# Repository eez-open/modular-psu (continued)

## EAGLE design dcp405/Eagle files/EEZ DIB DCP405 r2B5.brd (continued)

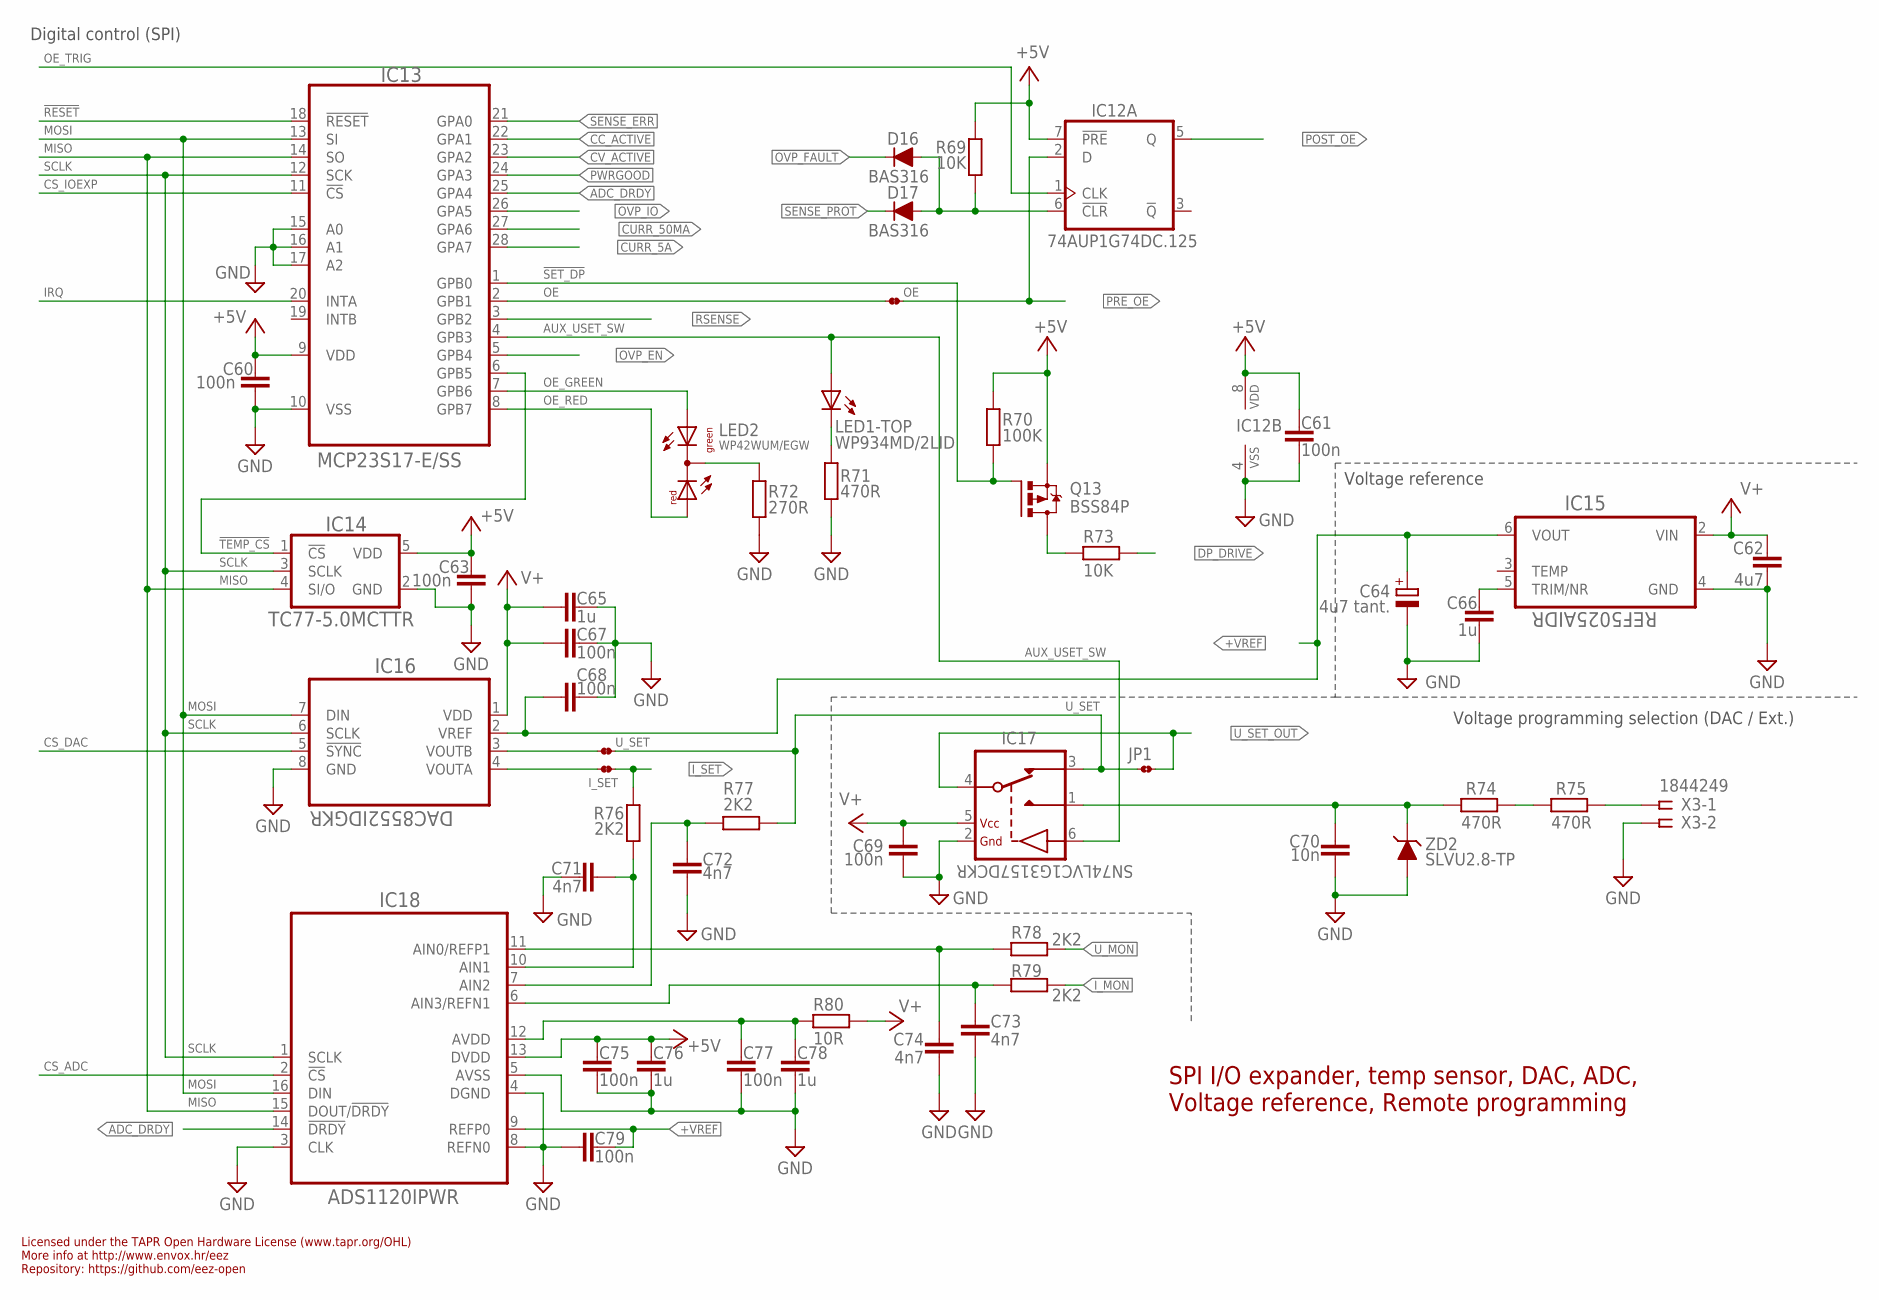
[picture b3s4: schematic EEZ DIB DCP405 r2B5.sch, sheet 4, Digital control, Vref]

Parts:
C60, C61, C63, C67, C68, C69, C75, C77, C79: 100n; C0603
C62: 4u7; C1206
C64: 4u7 tant.; EC1206
C65, C66, C76, C78: 1u; C0805
C70: 10n; C0805
C71, C72, C73, C74: 4n7; C0805
D16, D17: BAS316; SOD323-R
IC12: 74AUP1G74DC.125; DCU8
IC13: MCP23S17-E/SS; SOP65P780X200-28N
IC14: TC77-5.0MCTTR; SOT23-5
IC15: REF5025AIDR; SOIC127P600X175-8N
IC16: DAC8552IDGKR; DGK8-M
IC17: SN74LVC1G3157DCKR; SOT65P210X110-6N
IC18: ADS1120IPWR; PW(R-PDSO-G16)
I_SET: JP2-NOCUT
JP1: JP2-CUT
LED1: WP934MD/2LID; WP934MD
LED2: WP42WUM/EGW; L-42WUM-1EGWT
OE: JP2-NOCUT
Q13: BSS84P; SOT95P237X112-3N
R69, R73: 10K; R0805
R70: 100K; R0805
R71, R74, R75: 470R; R0805
R72: 270R; R0805
R76, R77, R78, R79: 2K2; R0805
R80: 10R; R1206
U_SET: JP2-NOCUT
X3: 1844249; MC1,5/5-G-3,5
ZD2: SLVU2.8-TP; SOT23

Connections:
!ADC_DRDY: IC13.25 (GPA4), IC18.14 (!DRDY)
!DP_DRIVE: R73.1; also elsewhere on the board
!OVP_FAULT: D16.C; also elsewhere on the board
!RESET: IC13.18 (!RESET); also elsewhere on the board
!SET_DP: IC13.1 (GPB0), Q13.1 (G), R70.2
!TEMP_CS: IC13.6 (GPB5), IC14.1 (!CS)
+5V: C60.1, C61.2, C63.1, C75.2, C76.2, IC12.7 (!PRE), IC12.8 (VDD), IC13.9 (VDD), IC14.5 (VDD), IC18.13 (DVDD), Q13.2 (S), R69.1, R70.1; also elsewhere on the board
+VREF: C64.+, C68.2, C79.2, IC15.6 (VOUT), IC16.2 (VREF), IC18.9 (REFP0); also elsewhere on the board
AUX_IN: C70.2, IC17.1 (NO), R74.1, ZD2.3 (C)
AUX_USET_SW: IC13.4 (GPB3), IC17.6 (CTRL), LED1.TA (A)
CC_ACTIVE: IC13.22 (GPA1); also elsewhere on the board
CS_ADC: IC18.2 (!CS); also elsewhere on the board
CS_DAC: IC16.5 (!SYNC); also elsewhere on the board
CS_IOEXP: IC13.11 (!CS); also elsewhere on the board
CURR_5A: IC13.28 (GPA7); also elsewhere on the board
CURR_50MA: IC13.27 (GPA6); also elsewhere on the board
CV_ACTIVE: IC13.23 (GPA2); also elsewhere on the board
DP_LED: Q13.3 (D), R73.2
GND: C60.2, C61.1, C62.2, C63.2, C64.-, C65.2, C66.2, C67.1, C68.1, C69.2, C70.1, C71.1, C72.1, C73.2, C74.1, C75.1, C76.1, C77.1, C78.1, C79.1, IC12.4 (VSS), IC13.10 (VSS), IC13.15 (A0), IC13.16 (A1), IC13.17 (A2), IC14.2 (GND), IC15.4 (GND), IC16.8 (GND), IC17.2 (GND), IC18.3 (CLK), IC18.4 (DGND), IC18.5 (AVSS), IC18.8 (REFN0), R71.1, R72.2, X3.2, ZD2.1 (A), ZD2.2 (A); also elsewhere on the board
IRQ: IC13.20 (INTA); also elsewhere on the board
I_MON: R79.1; also elsewhere on the board
I_SET: I_SET.2, R76.1; also elsewhere on the board
MISO: IC13.14 (SO), IC14.4 (SI/O), IC18.15 (DOUT/!DRDY); also elsewhere on the board
MOSI: IC13.13 (SI), IC16.7 (DIN), IC18.16 (DIN); also elsewhere on the board
unnamed: LED2.CC (C), R72.1
unnamed: IC16.4 (VOUTA), I_SET.1
unnamed: R74.2, R75.1
unnamed: R75.2, X3.1
unnamed: IC16.3 (VOUTB), U_SET.1
unnamed: D16.A, D17.A, IC12.6 (!CLR), R69.2
unnamed: C77.2, C78.2, IC18.12 (AVDD), R80.2
unnamed: C66.1, IC15.5 (TRIM/NR)
unnamed: C71.2, IC18.10 (AIN1), R76.2
unnamed: C74.2, IC18.11 (AIN0/REFP1), R78.2
unnamed: C72.2, IC18.7 (AIN2), R77.2
unnamed: C73.1, IC18.6 (AIN3/REFN1), R79.2
unnamed: LED1.TC (C), R71.2
OE: IC13.2 (GPB1), OE.1
OE_GREEN: IC13.7 (GPB6), LED2.GREEN (AG)
OE_RED: IC13.8 (GPB7), LED2.RED (AR)
OE_TRIG: IC12.1 (CLK); also elsewhere on the board
OVP_EN: IC13.5 (GPB4); also elsewhere on the board
OVP_IO: IC13.26 (GPA5); also elsewhere on the board
POST_OE: IC12.5 (Q); also elsewhere on the board
PRE_OE: IC12.2 (D), OE.2; also elsewhere on the board
PWRGOOD: IC13.24 (GPA3); also elsewhere on the board
RSENSE: IC13.3 (GPB2); also elsewhere on the board
SCLK: IC13.12 (SCK), IC14.3 (SCLK), IC16.6 (SCLK), IC18.1 (SCLK); also elsewhere on the board
SENSE_ERR: IC13.21 (GPA0); also elsewhere on the board
SENSE_PROT: D17.C; also elsewhere on the board
U_MON: R78.1; also elsewhere on the board
U_SET: IC17.3 (NC), JP1.1, R77.1, U_SET.2; also elsewhere on the board
U_SET_OUT: IC17.4 (COM), JP1.2; also elsewhere on the board
V+: C62.1, C65.1, C67.2, C69.1, IC15.2 (VIN), IC16.1 (VDD), IC17.5 (VDD), R80.1; also elsewhere on the board

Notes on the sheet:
Digital control (SPI)
Voltage reference
Licensed under the TAPR Open Hardware License (www.tapr.org/OHL)
Repository: https://github.com/eez-open
More info at http://www.envox.hr/eez
SPI I/O expander, temp sensor, DAC, ADC, Voltage reference, Remote programming
Voltage programming selection (DAC / Ext.)

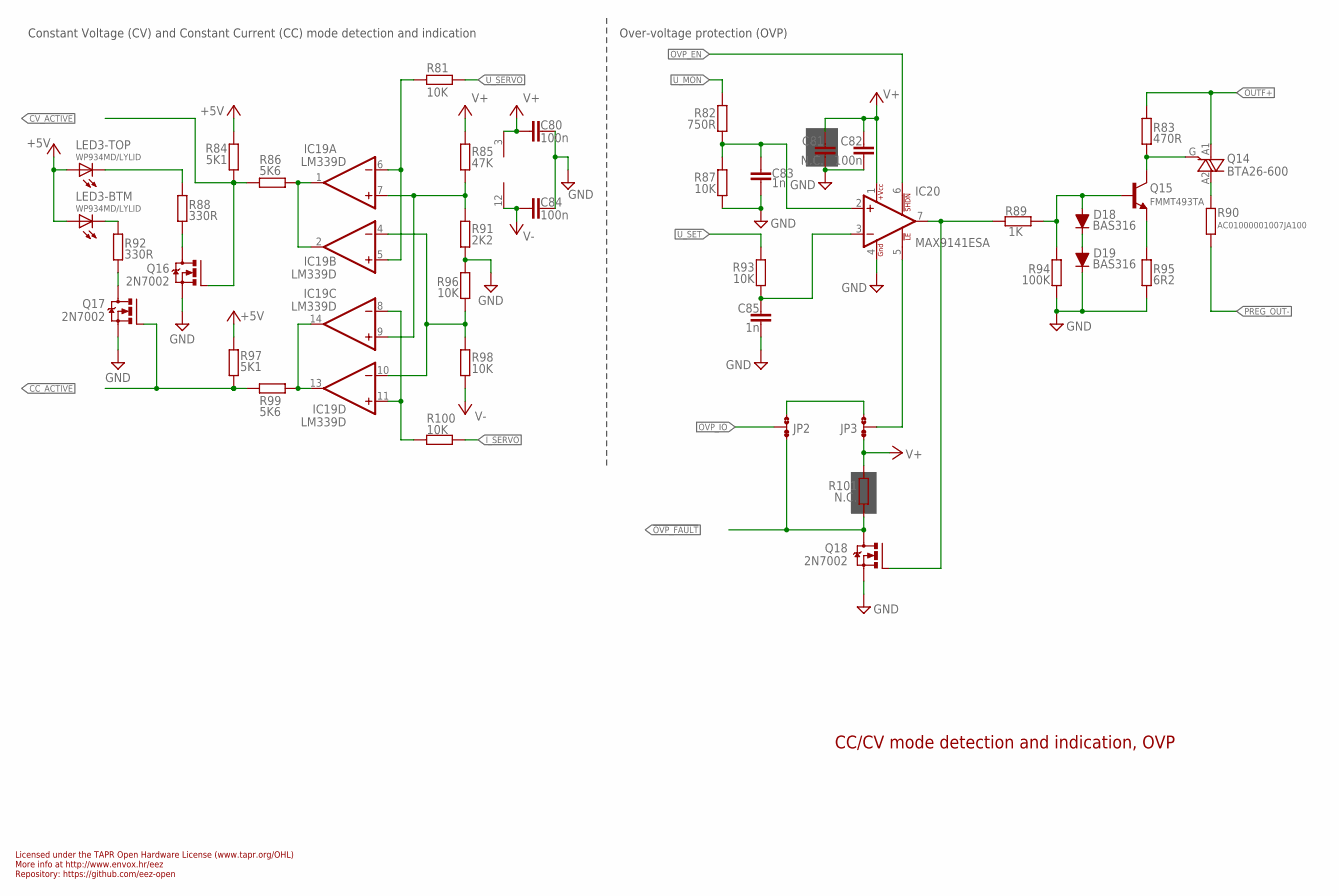
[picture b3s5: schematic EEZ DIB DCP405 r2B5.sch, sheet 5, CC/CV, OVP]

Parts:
C80, C82, C84: 100n; C0603
C81: N.C.; C0805
C83, C85: 1n; C0805
D18, D19: BAS316; SOD323-R
IC19: LM339D; SOIC127P600X175-14N
IC20: MAX9141ESA; SOIC127P600X173-8N
JP2: JP3-CUT-ROTATED; JP3-CUT2
JP3: JP3-CUT
LED3: WP934MD/LYLID; WP934MD
Q14: BTA26-600; TOP3_TRIAC_NOHOLE
Q15: FMMT493TA; SOT23-BEC
Q16, Q17: 2N7002; SOT103P240X110-3N
Q18: 2N7002; SOT103P240X110-3N; MPN 2N7002-7-F
R81, R87, R93, R96, R98, R100: 10K; R0805
R82: 750R; R0805
R83: 470R; R0805
R84, R97: 5K1; R0805
R85: 47K; R0805
R86, R99: 5K6; R0805
R88, R92: 330R; R0805
R89: 1K; R0805
R90: AC01000001007JA100; 0411/15
R91: 2K2; R0805
R94: 100K; R0805
R95: 6R2; R0805
R101: N.C.; R0805

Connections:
!OVP_FAULT: JP2.NC, Q18.3 (D), R101.2; also elsewhere on the board
+5V: LED3.BA (A), LED3.TA (A), R84.2, R97.2; also elsewhere on the board
CC_ACTIVE: Q17.1 (G), R97.1, R99.2; also elsewhere on the board
CC_LED: LED3.BC (C), R92.2
CV_ACTIVE: Q16.1 (G), R84.1, R86.2; also elsewhere on the board
CV_LED: LED3.TC (C), R88.1
GND: C80.1, C81.2, C82.1, C83.1, C84.1, C85.1, D19.C, IC20.4 (GND), Q16.2 (S), Q17.2 (S), Q18.2 (S), R87.2, R91.1, R94.1, R95.1, R96.2; also elsewhere on the board
I_SERVO: R100.1; also elsewhere on the board
unnamed: IC20.7 (OUT), Q18.1 (G), R89.2
unnamed: Q14.A2, R90.2
unnamed: Q14.G, Q15.C, R83.1
unnamed: Q15.E, R95.2
unnamed: D18.C, D19.A
unnamed: D18.A, Q15.B, R89.1, R94.2
unnamed: C85.2, IC20.3 (-IN), R93.2
unnamed: C83.2, IC20.2 (+IN), R82.2, R87.1
unnamed: Q17.3 (D), R92.1
unnamed: JP2.NO, JP3.NO
unnamed: IC20.5 (!LE), JP3.COM
unnamed: IC19.1 (OUT), IC19.2 (OUT), R86.1
unnamed: IC19.13 (OUT), IC19.14 (OUT), R99.1
unnamed: Q16.3 (D), R88.2
unnamed: IC19.5 (+IN), IC19.6 (-IN), R81.2
unnamed: IC19.8 (-IN), IC19.11 (+IN), R100.2
unnamed: IC19.7 (+IN), IC19.9 (+IN), R85.1, R91.2
unnamed: IC19.4 (-IN), IC19.10 (-IN), R96.1, R98.2
OUTF+: Q14.A1, R83.2; also elsewhere on the board
OVP_EN: IC20.6 (!SHDN); also elsewhere on the board
OVP_IO: JP2.COM; also elsewhere on the board
PREG_OUT-: R90.1; also elsewhere on the board
U_MON: R82.1; also elsewhere on the board
U_SERVO: R81.1; also elsewhere on the board
U_SET: R93.1; also elsewhere on the board
V+: C80.2, C81.1, C82.2, IC19.3 (V+), IC20.1 (+VCC), JP3.NC, R85.2, R101.1; also elsewhere on the board
V-: C84.2, IC19.12 (GND), R98.1; also elsewhere on the board

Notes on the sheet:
Licensed under the TAPR Open Hardware License (www.tapr.org/OHL)
Repository: https://github.com/eez-open
More info at http://www.envox.hr/eez
CC/CV mode detection and indication, OVP
Constant Voltage (CV) and Constant Current (CC) mode detection and indication
Over-voltage protection (OVP)

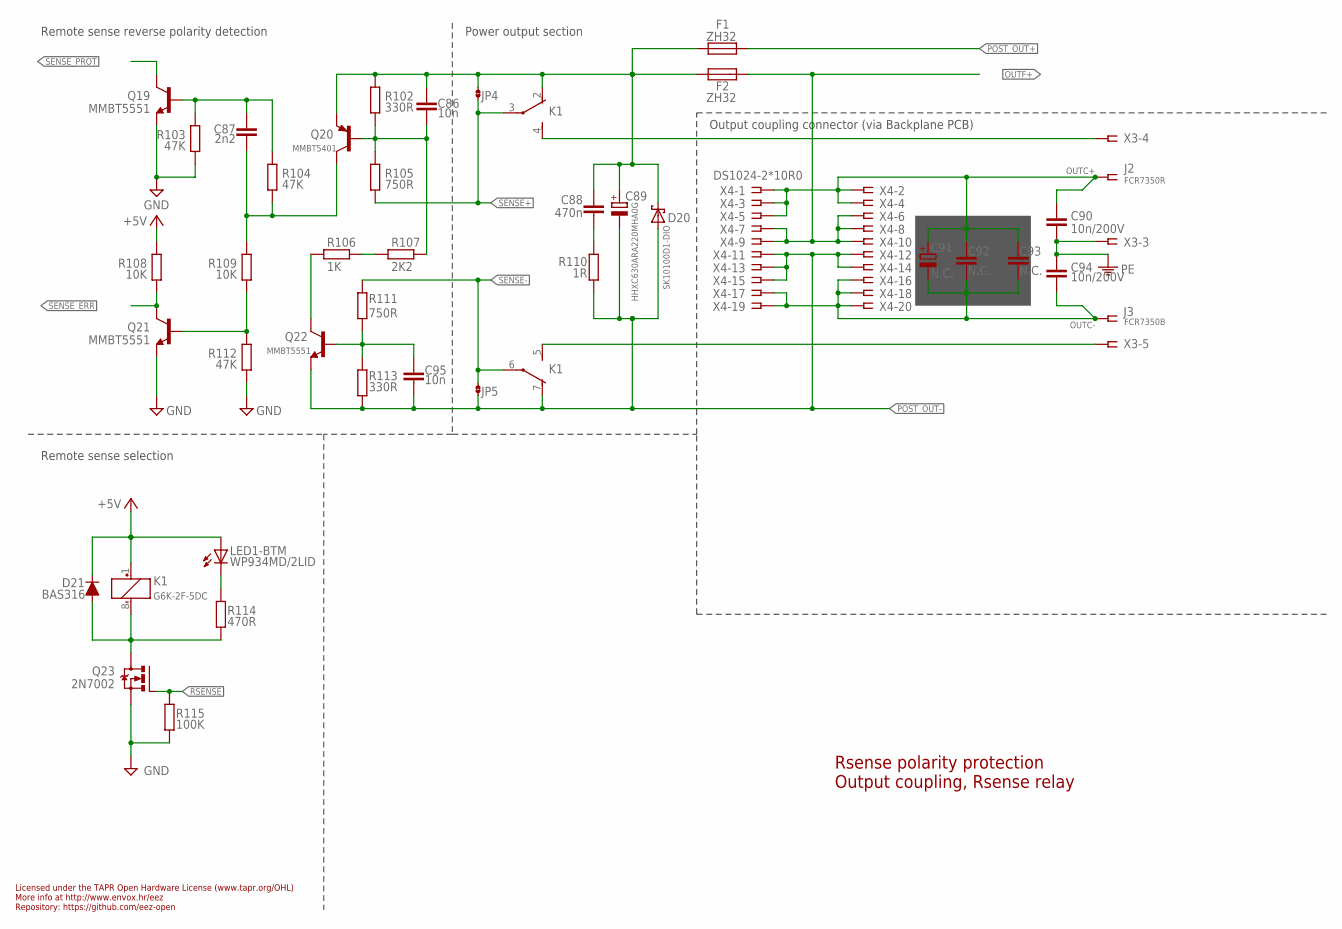
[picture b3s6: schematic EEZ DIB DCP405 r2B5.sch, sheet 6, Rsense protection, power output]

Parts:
C86, C95: 10n; C0805
C87: 2n2; C0805
C88: 470n; C1206
C89: HHXC630ARA220MHA0G; CAPAE830X1050N
C90, C94: 10n/200V; C1206
C91: N.C.; ECAP2/5
C92, C93: N.C.; C0805
D20: SK10100D1-DIO; TO252-L
D21: BAS316; SOD323-R
F1, F2: ZH32
J2: FCR7350R; S16N-PC
J3: FCR7350B; S16N-PC
JP4, JP5: JP2-CUT
K1: G6K-2F-5DC; G6K-2F; MPN G6K-2F DC24
LED1: WP934MD/2LID; WP934MD
Q19, Q21, Q22: MMBT5551; SOT23-BEC
Q20: MMBT5401; SOT23-BEC
Q23: 2N7002; SOT103P240X110-3N; MPN 2N7002-7-F
R102, R113: 330R; R0805
R103, R104, R112: 47K; R0805
R105, R111: 750R; R0805
R106: 1K; R0805
R107: 2K2; R0805
R108, R109: 10K; R0805
R110: 1R; R0805
R114: 470R; R0805
R115: 100K; R0805
X3: 1844249; MC1,5/5-G-3,5
X4: DS1024-2*10R0; SSW-110-02-T-D-RA

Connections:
+5V: D21.C, K1.1 (+), LED1.BA (A), R108.2; also elsewhere on the board
GND: Q19.E, Q21.E, Q23.2 (S), R103.1, R112.1, R115.1; also elsewhere on the board
unnamed: C86.2, Q20.B, R102.1, R105.2, R107.2
unnamed: C87.2, Q20.C, R104.1, R109.2
unnamed: Q22.C, R106.1
unnamed: C95.1, Q22.B, R111.1, R113.2
unnamed: C87.1, Q19.B, R103.2, R104.2
unnamed: Q21.B, R109.1, R112.2
unnamed: C88.2, R110.2
unnamed: D21.A, K1.8 (-), Q23.3 (D), R114.1
unnamed: K1.4 (S), X3.4
unnamed: K1.5 (S), X3.5
unnamed: LED1.BC (C), R114.2
unnamed: R106.2, R107.1
OUTC+: C90.1, C91.+, C92.1, C93.1, J2.1, J2.NC1, J2.NC2, J2.NC3, J2.NC4, X4.1, X4.2, X4.3, X4.4, X4.5
OUTC-: C91.-, C92.2, C93.2, C94.2, J3.1, J3.NC1, J3.NC2, J3.NC3, J3.NC4, X4.16, X4.17, X4.18, X4.19, X4.20
OUTF+: F2.2, X4.6, X4.7, X4.8, X4.9, X4.10; also elsewhere on the board
PE: C90.2, C94.1, X3.3; also elsewhere on the board
POST_OUT+: F1.1; also elsewhere on the board
POST_OUT-: C89.-, C95.2, D20.1 (A), D20.2 (A), JP5.1, K1.7 (O), Q22.E, R110.1, R113.1, X4.11, X4.12, X4.13, X4.14, X4.15; also elsewhere on the board
POST_OUTF+: C86.1, C88.1, C89.+, D20.3 (C), F1.2, F2.1, JP4.2, K1.2 (O), Q20.E, R102.2
RSENSE: Q23.1 (G), R115.2; also elsewhere on the board
SENSE+: JP4.1, K1.3, R105.1; also elsewhere on the board
SENSE-: JP5.2, K1.6, R111.2; also elsewhere on the board
SENSE_ERR: Q21.C, R108.1; also elsewhere on the board
SENSE_PROT: Q19.C; also elsewhere on the board

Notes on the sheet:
Rsense polarity protection Output coupling, Rsense relay
Licensed under the TAPR Open Hardware License (www.tapr.org/OHL)
Repository: https://github.com/eez-open
More info at http://www.envox.hr/eez
Remote sense reverse polarity detection
Remote sense selection
Output coupling connector (via Backplane PCB)
Power output section

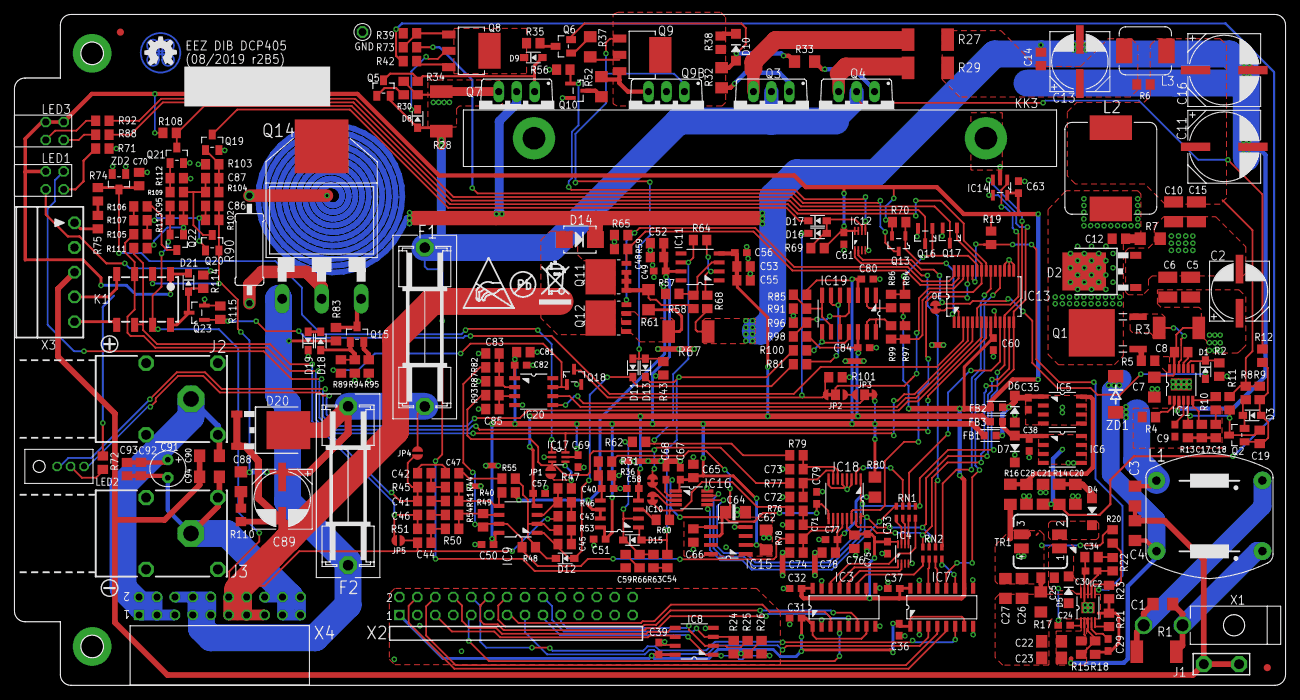
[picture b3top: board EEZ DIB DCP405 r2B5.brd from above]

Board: 2 copper layers, 180.0 x 95.0 mm, 320 parts (0 on the bottom side), 201 nets.

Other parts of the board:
EEZ_SIGNATURE: SIGNATURESMALL; SIGNATURE_5MM
U$1: RECYCLE_BIN1/8
U$6: ESD_SYMBOL
U$7: PB_SMALL

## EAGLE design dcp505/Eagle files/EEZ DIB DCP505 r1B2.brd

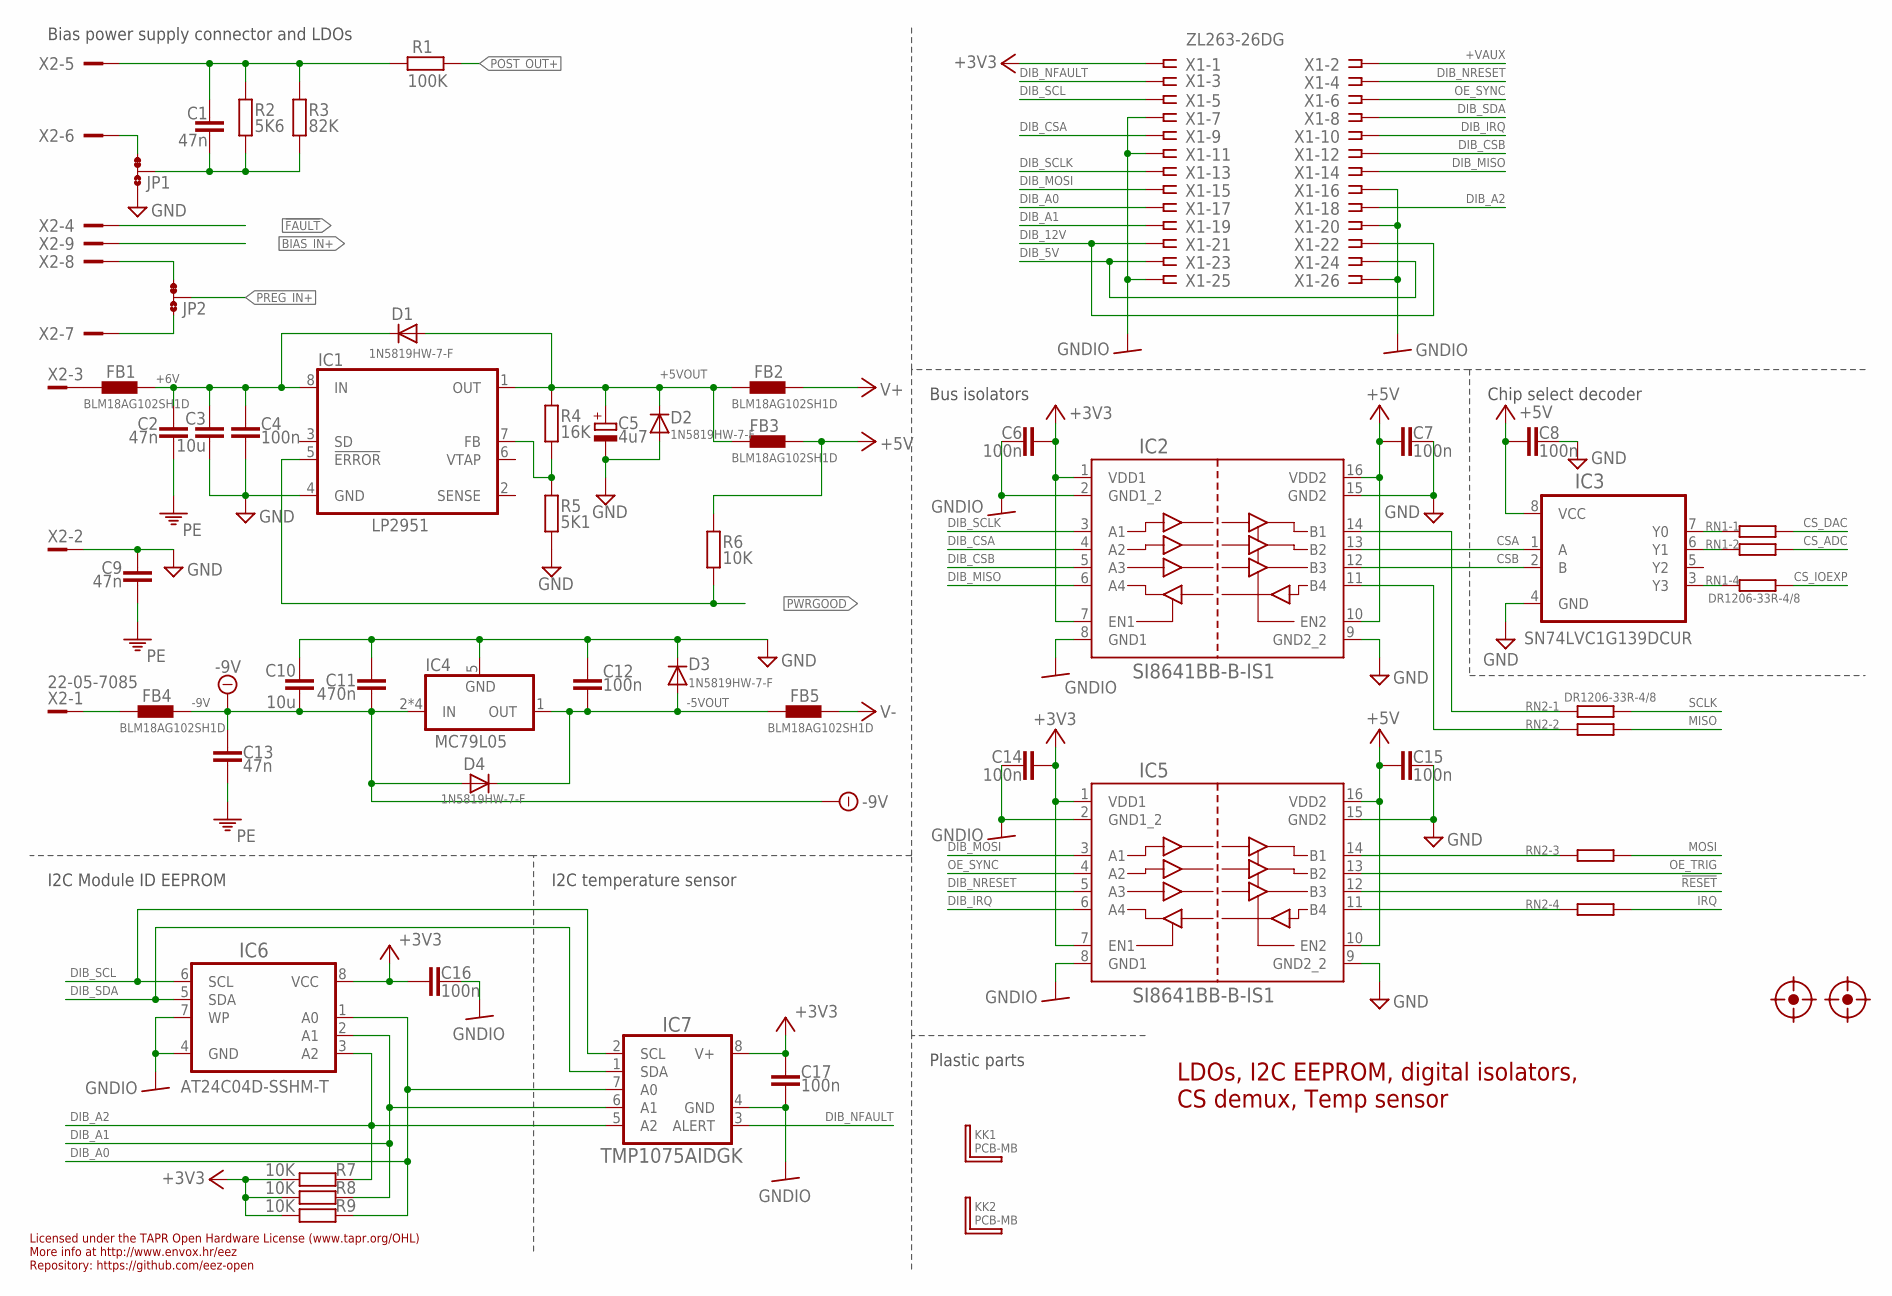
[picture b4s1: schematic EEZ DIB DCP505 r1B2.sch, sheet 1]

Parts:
C1: 47n; C0805
C2, C9, C13: 47n; C1206
C3, C10: 10u; C1206
C4, C6, C7, C8, C12, C14, C15, C16, C17: 100n; C0603
C5: 4u7; EC1206
C11: 470n; C0805
D1, D2, D3, D4: 1N5819HW-7-F; SOD323-W
FB1, FB2, FB3, FB4, FB5: BLM18AG102SH1D; BEAD0603
FM1, FM2: FIDUCIAL_2; FIDUCIAL_DUAL
IC1: LP2951; SOIC127P600X175-8N
IC2, IC5: SI8641BB-B-IS1; SOIC-16
IC3: SN74LVC1G139DCUR; DCU8
IC4: MC79L05; SOIC127P600X173-8N
IC6: AT24C04D-SSHM-T; SOIC127P600X173-8N
IC7: TMP1075AIDGK; DGK8
JP1, JP2: JP3-CUT
KK1, KK2: PCB-MB
R1: 100K; R0805
R2: 5K6; R0805
R3: 82K; R0805
R4: 16K; R0805
R5: 5K1; R0805
R6, R7, R8, R9: 10K; R0805
RN1, RN2: DR1206-33R-4/8; CAY16
X1: ZL263-26DG; SSW-113-02-T-D-RA
X2: 22-05-7085; SPOX_22-05-7095

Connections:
!FAULT: X2.4; also elsewhere on the board
!RESET: IC5.12 (B3); also elsewhere on the board
+3V3: C6.1, C14.1, C16.2, C17.1, IC2.1 (VDD1), IC2.7 (EN1), IC5.1 (VDD1), IC5.7 (EN1), IC6.8 (VCC), IC7.8 (V+), R7.1, R8.1, R9.1, X1.1
+5V: C7.2, C8.1, C15.2, FB3.P$2 (2), IC2.10 (EN2), IC2.16 (VDD2), IC3.8 (VCC), IC5.10 (EN2), IC5.16 (VDD2), R6.1; also elsewhere on the board
+5VOUT: C5.+, D1.A, D2.C, FB2.P$1 (1), FB3.P$1 (1), IC1.1 (OUT), R4.1
+6V: C2.1, C3.1, C4.1, D1.C, FB1.P$2 (2), IC1.8 (IN)
+VAUX: X1.2
-5VOUT: C12.2, D3.A, D4.C, FB5.P$1 (1), IC4.1 (OUT)
-9V: C10.2, C11.2, C13.1, D4.A, FB4.P$2 (2), IC4.2 (IN), IC4.3 (IN), IC4.6 (IN), IC4.7 (IN); also elsewhere on the board
BIAS_IN+: X2.9; also elsewhere on the board
CSA: IC2.13 (B2), IC3.1 (A)
CSB: IC2.12 (B3), IC3.2 (B)
CS_ADC: RN1.7 (2); also elsewhere on the board
CS_DAC: RN1.8 (2); also elsewhere on the board
CS_IOEXP: RN1.5 (2); also elsewhere on the board
DIB_5V: X1.23, X1.24
DIB_12V: X1.21, X1.22
DIB_A0: IC6.1 (A0), IC7.7 (A0), R9.2, X1.17
DIB_A1: IC6.2 (A1), IC7.6 (A1), R8.2, X1.19
DIB_A2: IC6.3 (A2), IC7.5 (A2), R7.2, X1.18
DIB_CSA: IC2.4 (A2), X1.9
DIB_CSB: IC2.5 (A3), X1.12
DIB_IRQ: IC5.6 (A4), X1.10
DIB_MISO: IC2.6 (A4), X1.14
DIB_MOSI: IC5.3 (A1), X1.15
DIB_NFAULT: IC7.3 (ALERT), X1.3
DIB_NRESET: IC5.5 (A3), X1.4
DIB_SCL: IC6.6 (SCL), IC7.2 (SCL), X1.5
DIB_SCLK: IC2.3 (A1), X1.13
DIB_SDA: IC6.5 (SDA), IC7.1 (SDA), X1.8
GND: C3.2, C4.2, C5.-, C7.1, C8.2, C9.1, C10.1, C11.1, C12.1, C15.1, D2.A, D3.C, IC1.4 (GND), IC2.9 (GND2_2), IC2.15 (GND2), IC3.4 (GND), IC4.5 (GND), IC5.9 (GND2_2), IC5.15 (GND2), JP1.NO, R5.2, X2.2; also elsewhere on the board
GNDIO: C6.2, C14.2, C16.1, C17.2, IC2.2 (GND1_2), IC2.8 (GND1), IC5.2 (GND1_2), IC5.8 (GND1), IC6.4 (GND), IC6.7 (WP), IC7.4 (GND), X1.7, X1.11, X1.16, X1.20, X1.25, X1.26
IRQ: RN2.5 (2); also elsewhere on the board
MISO: RN2.7 (2); also elsewhere on the board
MOSI: RN2.6 (2); also elsewhere on the board
unnamed: FB1.P$1 (1), X2.3
unnamed: FB4.P$1 (1), X2.1
unnamed: IC3.7 (Y0), RN1.1
unnamed: IC2.11 (B4), RN2.2 (1)
unnamed: IC5.11 (B4), RN2.4 (1)
unnamed: C1.2, JP1.COM, R2.2, R3.2
unnamed: C1.1, R1.2, R2.1, R3.1, X2.5
unnamed: IC3.6 (Y1), RN1.2 (1)
unnamed: IC3.3 (Y3), RN1.4 (1)
unnamed: JP1.NC, X2.6
unnamed: IC5.14 (B1), RN2.3 (1)
unnamed: JP2.NO, X2.7
unnamed: JP2.NC, X2.8
unnamed: IC1.7 (FB), R4.2, R5.1
unnamed: IC2.14 (B1), RN2.1
OE_SYNC: IC5.4 (A2), X1.6
OE_TRIG: IC5.13 (B2); also elsewhere on the board
PE: C2.2, C9.2, C13.2; also elsewhere on the board
POST_OUT+: R1.1; also elsewhere on the board
PREG_IN+: JP2.COM; also elsewhere on the board
PWRGOOD: IC1.5 (!ERROR), R6.2; also elsewhere on the board
SCLK: RN2.8 (2); also elsewhere on the board
V+: FB2.P$2 (2); also elsewhere on the board
V-: FB5.P$2 (2); also elsewhere on the board

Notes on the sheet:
Licensed under the TAPR Open Hardware License (www.tapr.org/OHL)
Repository: https://github.com/eez-open
More info at http://www.envox.hr/eez
I2C Module ID EEPROM
Bus isolators
LDOs, I2C EEPROM, digital isolators,
Plastic parts
Chip select decoder
Bias power supply connector and LDOs
I2C temperature sensor
CS demux, Temp sensor

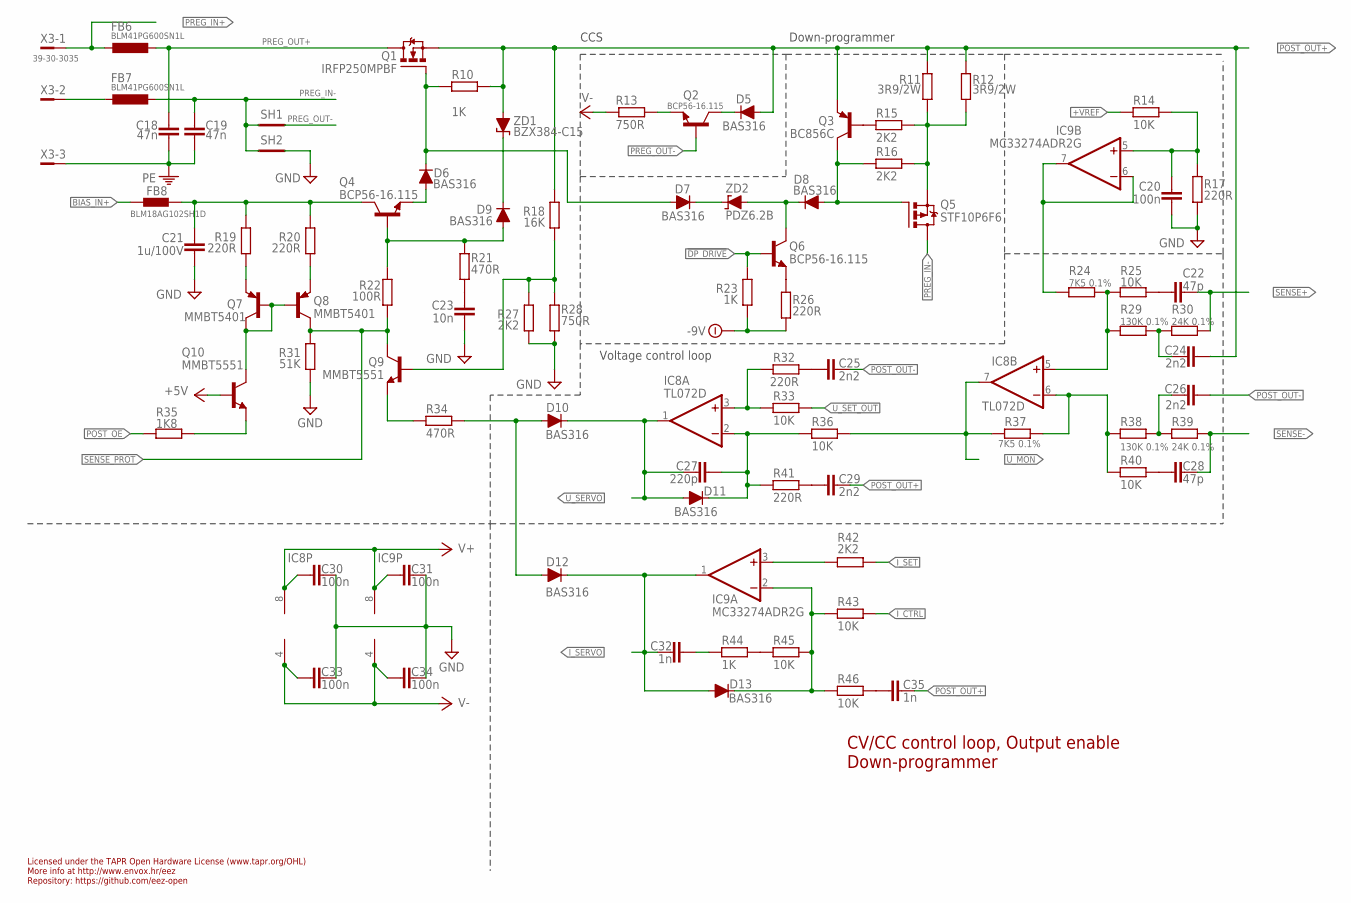
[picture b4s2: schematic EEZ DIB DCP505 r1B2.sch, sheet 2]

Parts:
C18, C19: 47n; C1206
C20, C30, C31, C33, C34: 100n; C0603
C21: 1u/100V; C1206
C22, C28: 47p; C0805
C23: 10n; C0805
C24, C25, C26, C29: 2n2; C0805
C27: 220p; C0805
C32, C35: 1n; C0805
D5, D6, D7, D8, D9, D10, D11, D12, D13: BAS316; SOD323-R
FB6, FB7: BLM41PG600SN1L; L1812
FB8: BLM18AG102SH1D; BEAD0603
IC8: TL072D; SOIC127P600X173-8N
IC9: MC33274ADR2G; SOIC127P600X173-8N
Q1: IRFP250MPBF; TO247BH-CLR2
Q2, Q4, Q6: BCP56-16.115; SOT230P700X180-4N
Q3: BC856C; SOT23-BEC
Q5: STF10P6F6; TO220H-CLR2
Q7, Q8: MMBT5401; SOT23-BEC
Q9, Q10: MMBT5551; SOT23-BEC
R10, R23, R44: 1K; R0805
R11, R12: 3R9/2W; R2512
R13, R28: 750R; R0805
R14, R25, R33, R36, R40, R43, R45, R46: 10K; R0805
R15, R16, R27, R42: 2K2; R0805
R17, R19, R20, R26, R32, R41: 220R; R0805
R18: 16K; R0805
R21, R34: 470R; R0805
R22: 100R; R0805
R24, R37: 7K5 0.1%; R0805
R29, R38: 130K 0.1%; R0805
R30, R39: 24K 0.1%; R0805
R31: 51K; R0805
R35: 1K8; R0805
SH1, SH2: SHORTNOHOLE; SHORT_NOHOLE
X3: 39-30-3035; MINIFIT_6659-3
ZD1: BZX384-C15; SOD323-W
ZD2: PDZ6.2B; SOD323-W

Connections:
!DP_DRIVE: Q6.1 (B), R23.1; also elsewhere on the board
+5V: Q10.B; also elsewhere on the board
+VREF: R14.1; also elsewhere on the board
-9V: R23.2, R26.2; also elsewhere on the board
BIAS_IN+: FB8.P$1 (1); also elsewhere on the board
CCS_HS: D5.C, Q2.2 (C), Q2.4 (C)
DC_BIAS: C21.1, FB8.P$2 (2), Q4.2 (C), Q4.4 (C), R19.2, R20.2
DP_S: Q5.3 (S), R11.1, R12.1, R15.1, R16.1
GCOM: IC9.6 (-IN), IC9.7 (OUT), R24.1
GND: C20.2, C21.2, C23.2, C30.1, C31.1, C33.1, C34.1, R17.2, R27.1, R28.1, R31.1, SH2.P$2 (GND_B); also elsewhere on the board
I_CTRL: R43.1; also elsewhere on the board
I_SERVO: C32.2, D12.C, D13.A, IC9.1 (OUT); also elsewhere on the board
I_SET: R42.1; also elsewhere on the board
LOOP_CTRL: D10.A, D12.A, R34.1
unnamed: FB7.1, X3.2
unnamed: IC9.3 (+IN), R42.2
unnamed: IC8.3 (+IN), R32.2, R33.2
unnamed: C27.1, D11.C, IC8.2 (-IN), R36.2, R41.2
unnamed: C26.1, R38.2, R39.1
unnamed: C22.2, R25.1
unnamed: C28.2, R40.1
unnamed: C35.2, R46.1
unnamed: D13.C, IC9.2 (-IN), R43.2, R45.2, R46.2
unnamed: C25.2, R32.1
unnamed: C29.2, R41.1
unnamed: D6.C, D7.A, Q1.1 (G), R10.1
unnamed: D6.A, Q4.3 (E)
unnamed: D9.A, Q4.1 (B), R21.2, R22.1
unnamed: C23.1, R21.1
unnamed: Q9.B, R18.1, R27.2, R28.2
unnamed: Q6.3 (E), R26.1
unnamed: Q3.B, R15.2
unnamed: C20.1, IC9.5 (+IN), R14.2, R17.1
unnamed: C24.1, R29.2, R30.1
unnamed: D9.C, ZD1.C
unnamed: D7.C, ZD2.C
unnamed: Q9.E, R34.2
unnamed: D8.A, Q3.C, Q5.1 (G), R16.2
unnamed: IC8.5 (+IN), R24.2, R25.2, R29.1
unnamed: IC8.6 (-IN), R37.2, R38.1, R40.2
unnamed: R44.2, R45.1
unnamed: C32.1, R44.1
unnamed: Q2.3 (E), R13.2
unnamed: Q8.E, R20.1
unnamed: Q7.E, R19.1
unnamed: Q10.E, R35.2
PE: C18.2, C19.2, X3.3; also elsewhere on the board
POST_OE: R35.1; also elsewhere on the board
POST_OUT+: C24.2, C29.1, C35.1, D5.A, Q1.3 (S), Q3.E, R10.2, R11.2, R12.2, R18.2, ZD1.A; also elsewhere on the board
POST_OUT-: C25.1, C26.2; also elsewhere on the board
PREG_IN+: FB6.1, X3.1; also elsewhere on the board
PREG_IN-: C19.1, FB7.2, Q5.2 (D), SH1.P$1 (GND_A), SH2.P$1 (GND_A)
PREG_OUT+: C18.1, FB6.2, Q1.2 (D)
PREG_OUT-: Q2.1 (B), SH1.P$2 (GND_B); also elsewhere on the board
Q6C: D8.C, Q6.2 (C), Q6.4 (C), ZD2.A
Q7C: Q7.B, Q7.C, Q8.B, Q10.C
SENSE+: C22.1, R30.2; also elsewhere on the board
SENSE-: C28.1, R39.2; also elsewhere on the board
SENSE_PROT: Q8.C, Q9.C, R22.2, R31.2; also elsewhere on the board
U_MON: IC8.7 (OUT), R36.1, R37.1; also elsewhere on the board
U_SERVO: C27.2, D10.C, D11.A, IC8.1 (OUT); also elsewhere on the board
U_SET_OUT: R33.1; also elsewhere on the board
V+: C30.2, C31.2, IC8.8 (V+), IC9.8 (V+); also elsewhere on the board
V-: C33.2, C34.2, IC8.4 (V-), IC9.4 (V-), R13.1; also elsewhere on the board

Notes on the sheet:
Voltage control loop
Down-programmer
Licensed under the TAPR Open Hardware License (www.tapr.org/OHL)
Repository: https://github.com/eez-open
More info at http://www.envox.hr/eez
CCS
CV/CC control loop, Output enable
